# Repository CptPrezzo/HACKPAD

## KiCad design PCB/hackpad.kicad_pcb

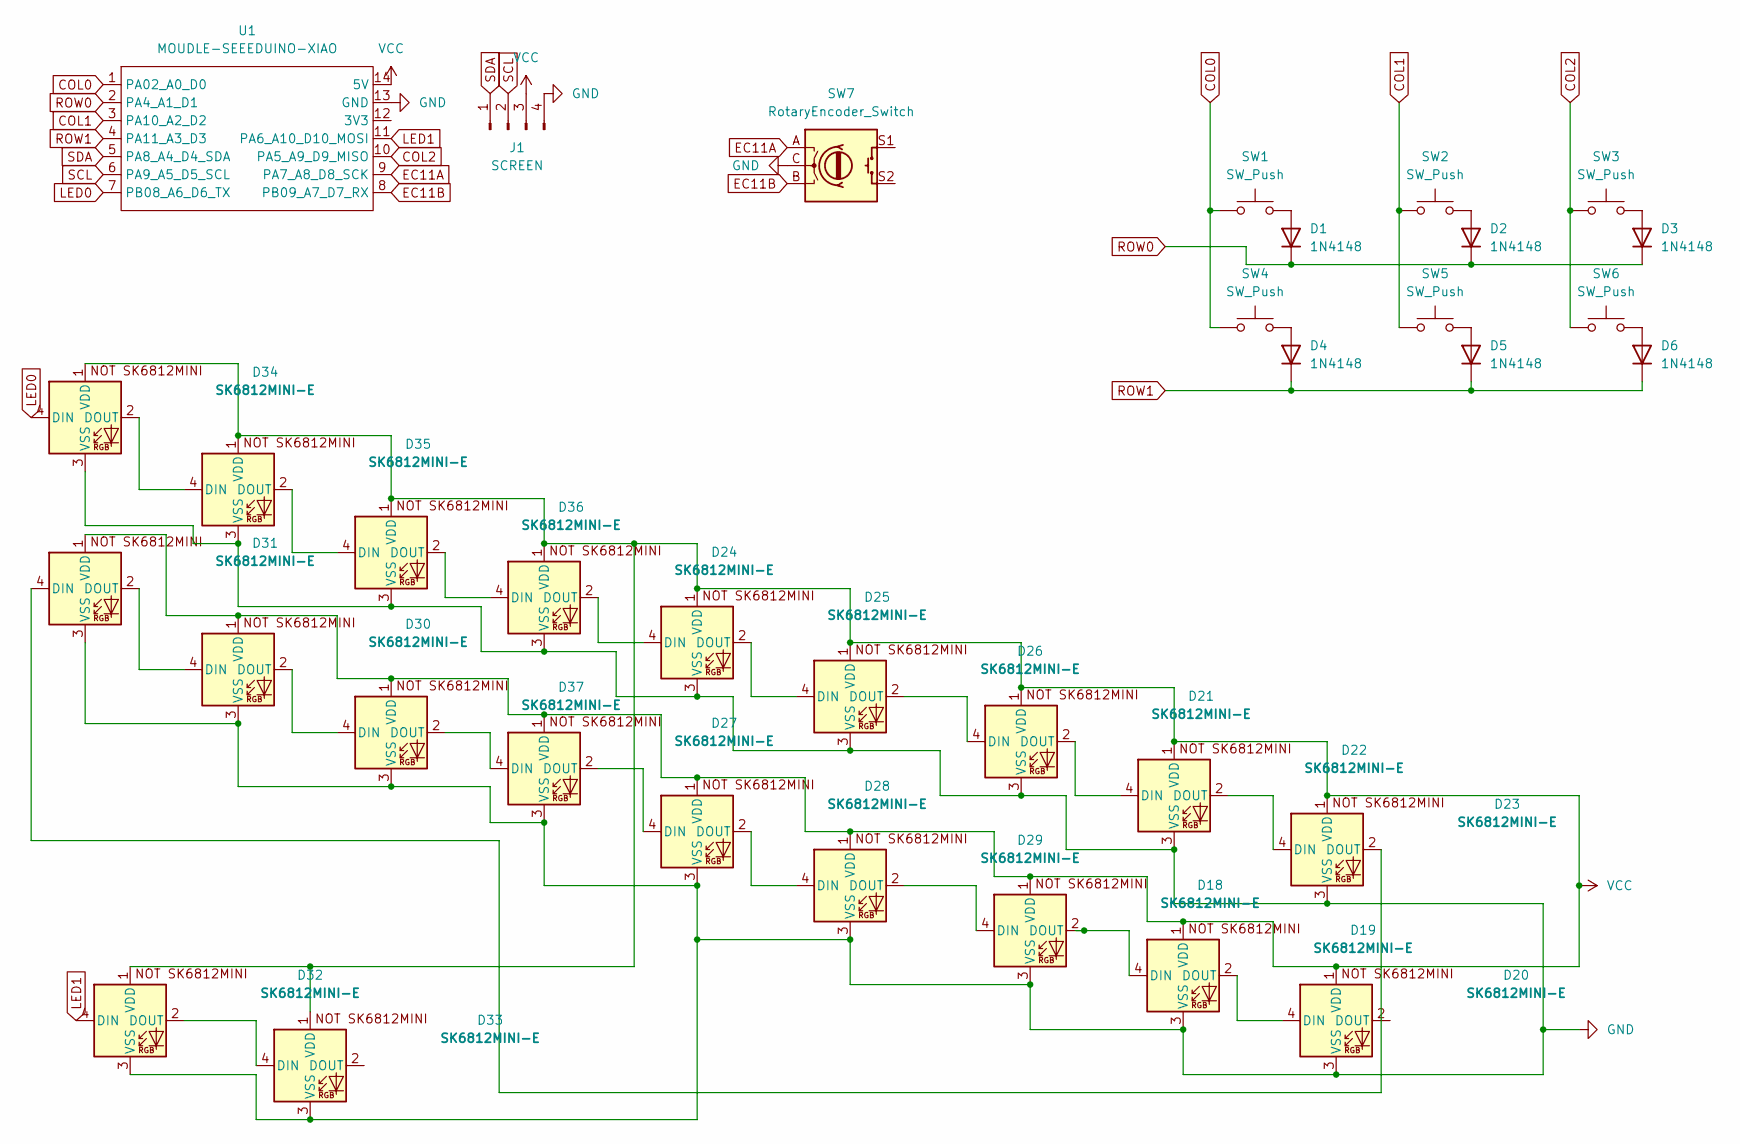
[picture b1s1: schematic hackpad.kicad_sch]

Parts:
D1, D2, D3, D4, D5, D6: 1N4148; D_DO-35_SOD27_P7.62mm_Horizontal
D18, D19, D20, D21, D22, D23, D24, D25, D26, D27, D28, D29, D30, D31, D32, D33, D34, D35, D36, D37: SK6812MINI-E; SK6812MINI-E_fixed
J1: SCREEN; OLED
SW1, SW2, SW3, SW4, SW5, SW6: SW_Push; MX-Solderable-1U
SW7: RotaryEncoder_Switch; RotaryEncoder_Alps_EC11E-Switch_Vertical_H20mm
U1: MOUDLE-SEEEDUINO-XIAO; XIAO-Generic-Hybrid-14P-2.54-21X17.8MM

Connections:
COL0: SW1.1, SW4.1, U1.1 (PA02_A0_D0)
COL1: SW2.1, SW5.1, U1.3 (PA10_A2_D2)
COL2: SW3.1, SW6.1, U1.10 (PA5_A9_D9_MISO)
EC11A: SW7.A, U1.9 (PA7_A8_D8_SCK)
EC11B: SW7.B, U1.8 (PB09_A7_D7_RX)
GND: D18.3 (VSS), D19.3 (VSS), D20.3 (VSS), D21.3 (VSS), D22.3 (VSS), D23.3 (VSS), D24.3 (VSS), D25.3 (VSS), D26.3 (VSS), D27.3 (VSS), D28.3 (VSS), D29.3 (VSS), D30.3 (VSS), D31.3 (VSS), D32.3 (VSS), D33.3 (VSS), D34.3 (VSS), D35.3 (VSS), D36.3 (VSS), D37.3 (VSS), J1.4, SW7.C, U1.13 (GND)
LED0: D34.4 (DIN), U1.7 (PB08_A6_D6_TX)
LED1: D32.4 (DIN), U1.11 (PA6_A10_D10_MOSI)
unnamed: D1.2 (A), SW1.2
unnamed: D2.2 (A), SW2.2
unnamed: D3.2 (A), SW3.2
unnamed: D4.2 (A), SW4.2
unnamed: D5.2 (A), SW5.2
unnamed: D6.2 (A), SW6.2
unnamed: D18.4 (DIN), D29.2 (DOUT)
unnamed: D18.2 (DOUT), D19.4 (DIN)
unnamed: D19.2 (DOUT), D20.4 (DIN)
unnamed: D21.4 (DIN), D26.2 (DOUT)
unnamed: D21.2 (DOUT), D22.4 (DIN)
unnamed: D22.2 (DOUT), D23.4 (DIN)
unnamed: D23.2 (DOUT), D31.4 (DIN)
unnamed: D24.4 (DIN), D36.2 (DOUT)
unnamed: D24.2 (DOUT), D25.4 (DIN)
unnamed: D25.2 (DOUT), D26.4 (DIN)
unnamed: D27.4 (DIN), D37.2 (DOUT)
unnamed: D27.2 (DOUT), D28.4 (DIN)
unnamed: D28.2 (DOUT), D29.4 (DIN)
unnamed: D30.4 (DIN), D31.2 (DOUT)
unnamed: D30.2 (DOUT), D37.4 (DIN)
unnamed: D32.2 (DOUT), D33.4 (DIN)
unnamed: D34.2 (DOUT), D35.4 (DIN)
unnamed: D35.2 (DOUT), D36.4 (DIN)
ROW0: D1.1 (K), D2.1 (K), D3.1 (K), U1.2 (PA4_A1_D1)
ROW1: D4.1 (K), D5.1 (K), D6.1 (K), U1.4 (PA11_A3_D3)
SCL: J1.2, U1.6 (PA9_A5_D5_SCL)
SDA: J1.1, U1.5 (PA8_A4_D4_SDA)
VCC: D18.1 (VDD), D19.1 (VDD), D20.1 (VDD), D21.1 (VDD), D22.1 (VDD), D23.1 (VDD), D24.1 (VDD), D25.1 (VDD), D26.1 (VDD), D27.1 (VDD), D28.1 (VDD), D29.1 (VDD), D30.1 (VDD), D31.1 (VDD), D32.1 (VDD), D33.1 (VDD), D34.1 (VDD), D35.1 (VDD), D36.1 (VDD), D37.1 (VDD), J1.3, U1.14 (5V)

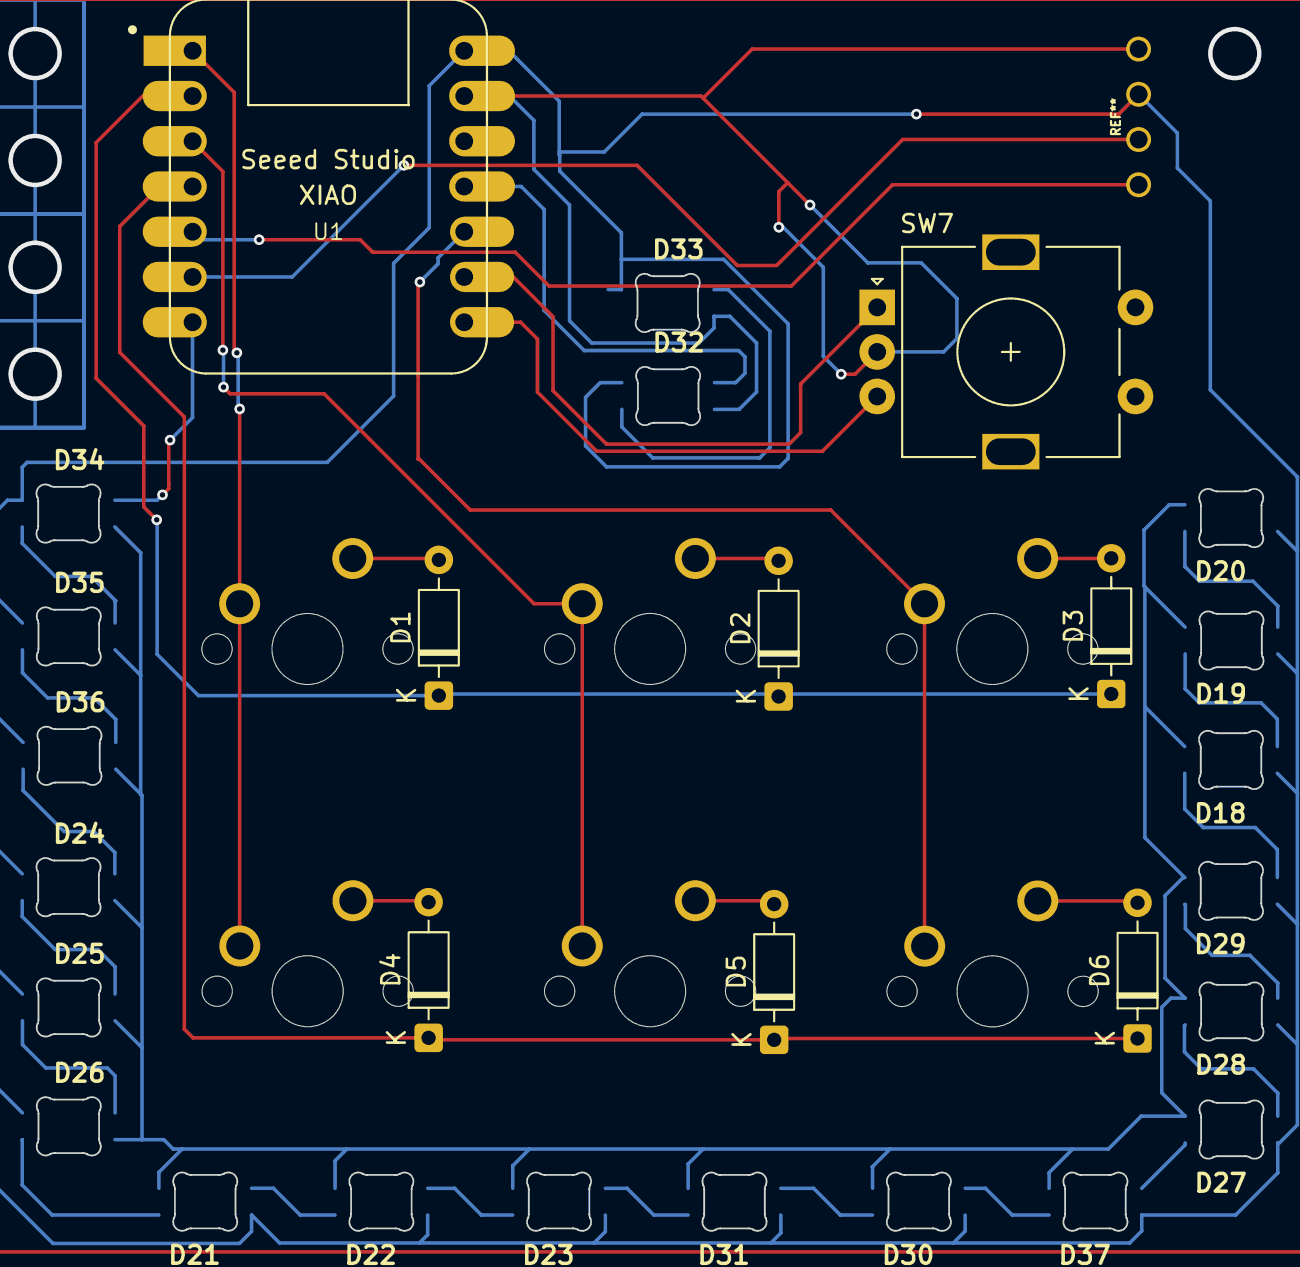
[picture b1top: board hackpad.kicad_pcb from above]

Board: 2 copper layers, 35 parts (0 on the bottom side), 37 nets.

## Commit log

2026-03-09 PCB
    this is the file .kicad for the pcb
2026-03-09 Create FIRMWARE
    this is the firmware for this hackpad
2026-03-09 CAD
    this is the folder for all the cad files
2026-03-09 Create OC
